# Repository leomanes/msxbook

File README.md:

# Msxbook side slot
(Msxbook external slot 2 adapter)

You are welcome to make and sell the adapter to the MSX community if you agree not to change the original files. 
Don't add new text or logos... don't change anything at all and it is all good.

Parts List:

-Main PCB: \
-- F1: 125ma to 375ma fuse (-12v line) \
-- F2: 800ma to 1A fuse (+5v line) \
-- F3: 400ma to 500ma fuse (+12v line) \
-- J1: 2x25 right angle pin header \
-- J2: 50 pin right angle male SCSI connector

***  The fuses are optional but recomended. If you don't want to use them, use a solid wire (old network cables are good donors).

-External PCB: \
-- C1: 100uf to 220uf 25v (optional)\
-- C2: 100uf to 220uf 25v (optional)\
-- C3: 220uf to 470uf 16v (optional)\
-- J1: 50 pin right angle edge connector\
-- J2: 50 pin right angle female SCSI connector

-3D brackets: (The dimentions below are critical. Get the correct ones.) \
--Screws are M2.5 x 5mm\
--Inserts are M2.5 x 2.5 x 3.5 

-Parts Link: \
https://a.aliexpress.com/_mOBWXzN \
https://www.aliexpress.us/item/2255800960638500.html (option: 2X25 50PIN) \
https://www.aliexpress.com/item/3256808357131162.html (option: M2.5x2.5x3.5) \
SCSI connectors: single or pack \
https://www.aliexpress.us/item/3256807779614080.html (option: 50 pin curved female and 50 pin curved male) \
https://a.aliexpress.com/_mt0LCd1 (option: 50 pin curved female and 50 pin curved male)

Tips and tricks: \
*** When soldering the EDGE connector, make sure the distance between the PCB and the connector is between 2mm and 3mm. \
*** The distance between the bottom of the main PCB and the top ot the angled pin header needs to be 7.3mm \
*** Make sure the angled pin header and EDGE connectors are at a nice 90°. Start by solderins pins 1, 2 and 49, 50 and then do a fit test and measure the distance mentioned above. \
*** To insert the pcb into the 3D cart, angle it 45° and insert the left side first ("left" when looking at inside the EDGE where the cart connects) then slide the board in, sitting it flush.

MSX FOREVER !!!

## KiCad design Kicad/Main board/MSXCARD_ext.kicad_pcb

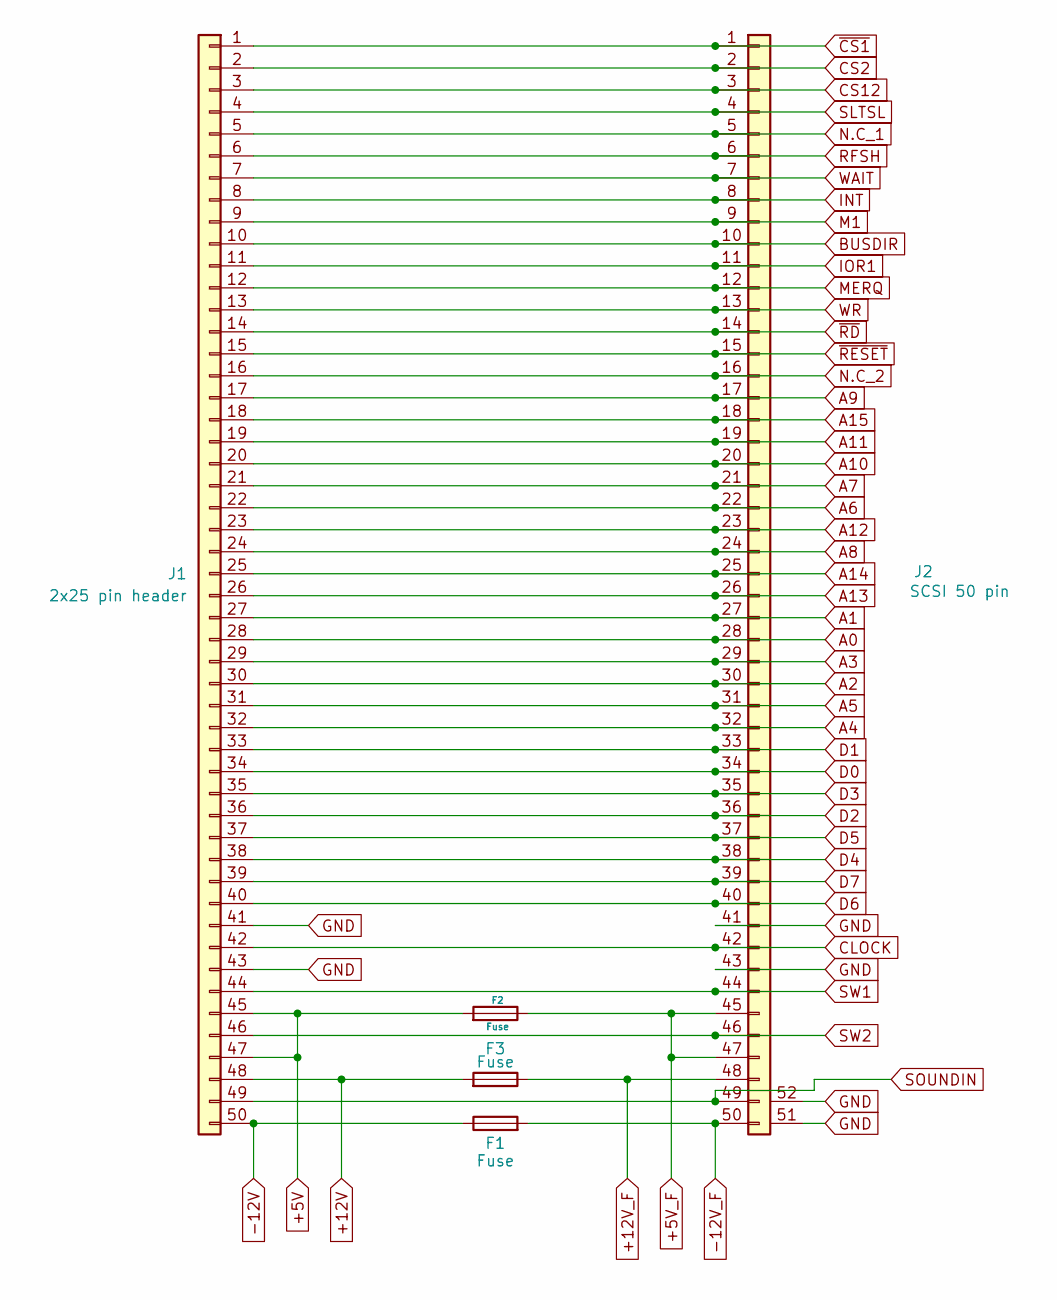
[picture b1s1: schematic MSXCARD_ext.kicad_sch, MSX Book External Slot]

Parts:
F1, F2, F3: Fuse; R_Axial_DIN0207_L6.3mm_D2.5mm_P10.16mm_Horizontal
J1: 2x25 pin header; PinHeader_2x25_P2.54mm_Vertical_trimmed_2
J2: SCSI 50 pin; SCSI_50_F

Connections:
+5V: F2.2, J1.45, J1.47
+5V_F: F2.1, J2.45, J2.47
+12V: F3.2, J1.48
+12V_F: F3.1, J2.48
-12V: F1.1, J1.50
-12V_F: F1.2, J2.50
A0: J1.28, J2.28
A1: J1.27, J2.27
A2: J1.30, J2.30
A3: J1.29, J2.29
A4: J1.32, J2.32
A5: J1.31, J2.31
A6: J1.22, J2.22
A7: J1.21, J2.21
A8: J1.24, J2.24
A9: J1.17, J2.17
A10: J1.20, J2.20
A11: J1.19, J2.19
A12: J1.23, J2.23
A13: J1.26, J2.26
A14: J1.25, J2.25
A15: J1.18, J2.18
BUSDIR: J1.10, J2.10
CLOCK: J1.42, J2.42
CS2: J1.2, J2.2
CS12: J1.3, J2.3
D0: J1.34, J2.34
D1: J1.33, J2.33
D2: J1.36, J2.36
D3: J1.35, J2.35
D4: J1.38, J2.38
D5: J1.37, J2.37
D6: J1.40, J2.40
D7: J1.39, J2.39
GND: J1.41, J1.43, J2.41, J2.43, J2.51 (Pin_49), J2.52 (Pin_50)
INT: J1.8, J2.8
IOR1: J1.11, J2.11
M1: J1.9, J2.9
MERQ: J1.12, J2.12
N.C_1: J1.5, J2.5
N.C_2: J1.16, J2.16
RFSH: J1.6, J2.6
SLTSL: J1.4, J2.4
SOUNDIN: J1.49, J2.49
SW1: J1.44, J2.44
SW2: J1.46, J2.46
WAIT: J1.7, J2.7
WR: J1.13, J2.13
~CS1: J1.1, J2.1
~RD: J1.14, J2.14
~RESET: J1.15, J2.15

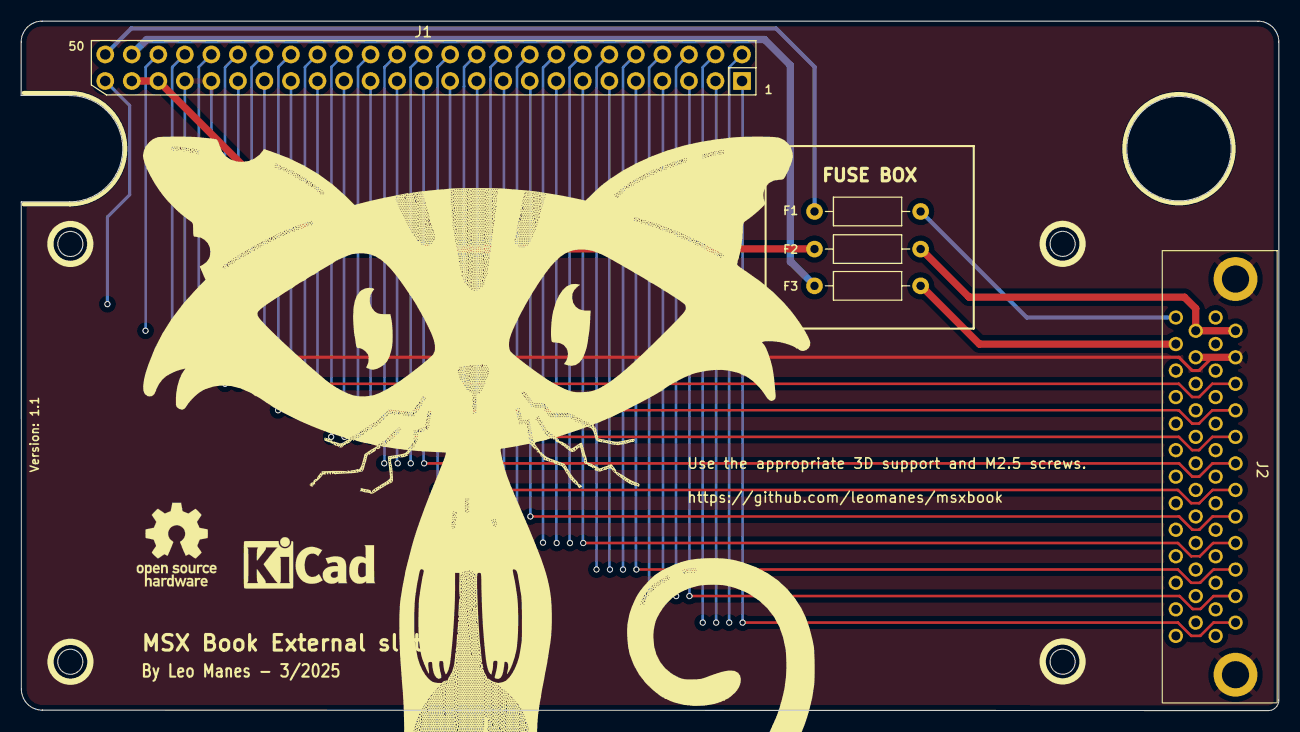
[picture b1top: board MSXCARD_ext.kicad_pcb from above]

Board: 4 copper layers, 120.4 x 66.0 mm, 5 parts (0 on the bottom side), 51 nets.

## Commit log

2025-05-21 MSX Book external cart adapter
2025-07-31 Add files via upload
    Insert holes tightened
